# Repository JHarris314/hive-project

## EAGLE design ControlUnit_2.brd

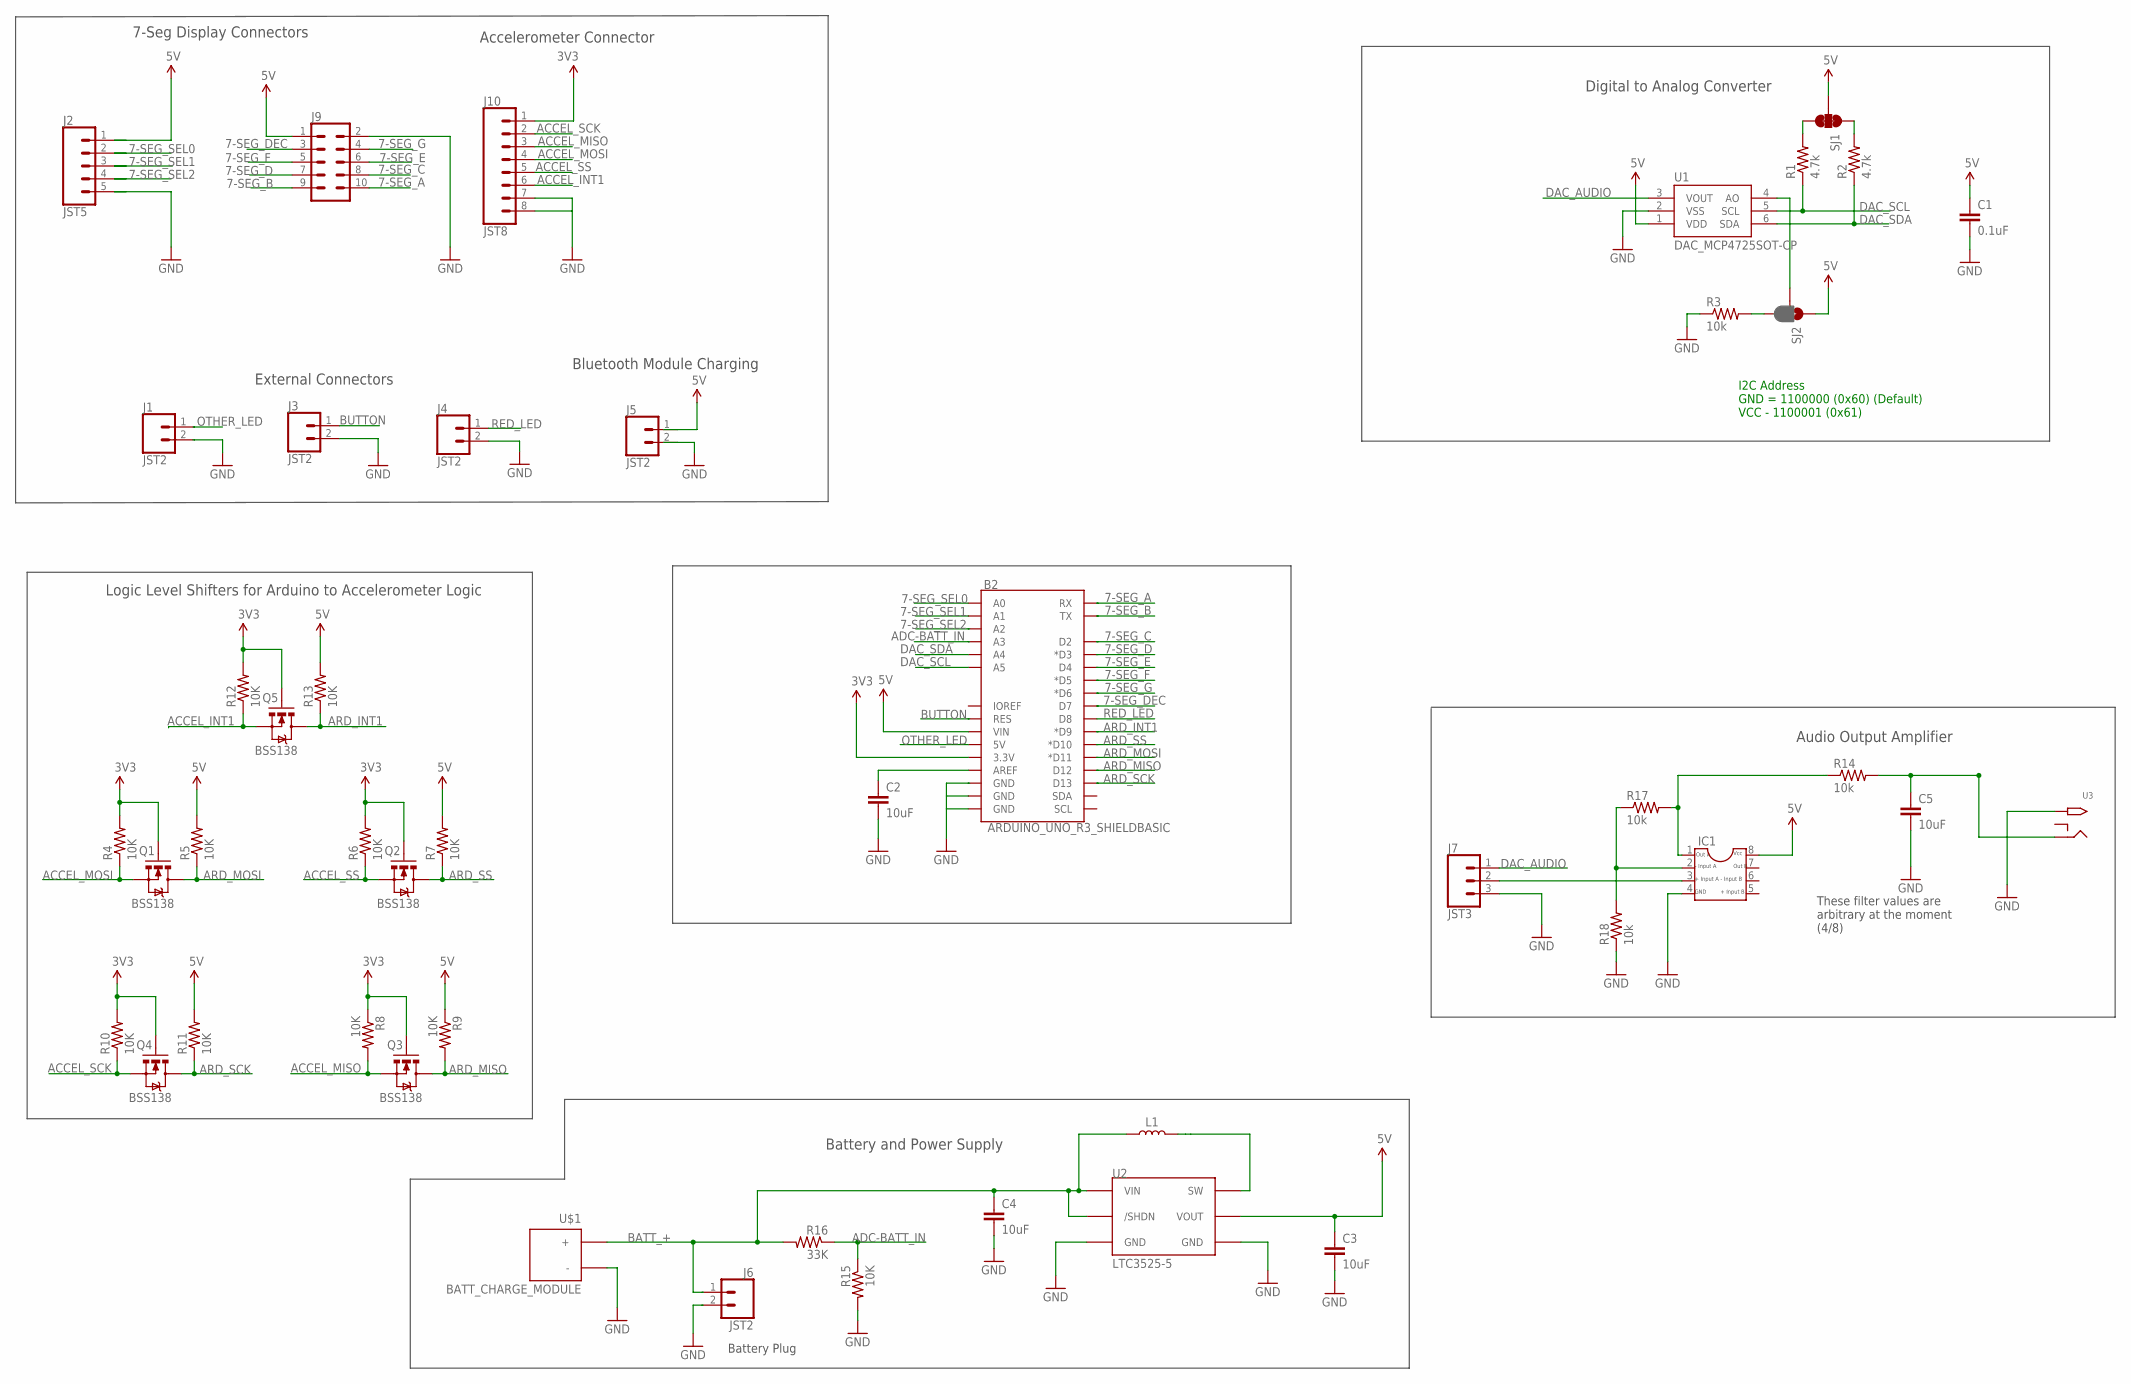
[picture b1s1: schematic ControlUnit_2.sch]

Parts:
B2: ARDUINO_UNO_R3_SHIELDBASIC; UNO_R3_SHIELD
C1: 0.1uF; 0603-CAP
C2, C4: 10uF; SPARKFUN_0805
C3, C5: 10uF; 0603-CAP
IC1: DIL8; DIL08
J1, J3, J4, J5, J6: JST2; 2JST
J2: JST5; 5JST
J7: JST3; 3JST
J9: CONN_05X2SHD_LOCK; 2X5-SHROUDED_LOCK
J10: JST8; 8JST
L1: 10uH; 1210
Q1, Q2, Q3, Q4, Q5: BSS138; SOT23-3
R1, R2: 4.7k; 0603-RES
R3, R14, R17, R18: 10k; 0603-RES
R4, R5, R6, R7, R10, R11, R12, R13: 10K; SPARKFUN_0603-RES
R8, R9, R15: 10K; 0603-RES
R16: 33K; 0603-RES
SJ1: JUMPER-PAD-3-NC_BY_TRACE; PAD-JUMPER-3-3OF3_NC_BY_TRACE_YES_SILK_FULL_BOX
SJ2: JUMPER-PAD-3-2OF3_NC_BY_PASTE; PAD-JUMPER-3-2OF3_NC_BY_PASTE_YES_SILK_FULL_BOX
U1: DAC_MCP4725SOT-CP; SOT23-6-MCP4725
U2: LTC3525-5
U3: MONO_JACK
U$1: BATT_CHARGE_MODULE

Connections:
3V3: B2.3.3V, J10.1, Q1.1 (G), Q2.1 (G), Q3.1 (G), Q4.1 (G), Q5.1 (G), R4.2, R6.2, R8.1, R10.2, R12.2
5V: B2.VIN, C1.1, C3.1, IC1.8, J2.1, J5.1, J9.1, R5.2, R7.2, R9.1, R11.2, R13.2, SJ1.2, SJ2.1, U1.1 (VDD), U2.4 (VOUT)
7-SEG_A: B2.RX, J9.10
7-SEG_B: B2.TX, J9.9
7-SEG_C: B2.D2, J9.8
7-SEG_D: B2.D3 (*D3), J9.7
7-SEG_DEC: B2.D7, J9.3
7-SEG_E: B2.D4, J9.6
7-SEG_F: B2.D5 (*D5), J9.5
7-SEG_G: B2.D6 (*D6), J9.4
7-SEG_SEL0: B2.A0, J2.2
7-SEG_SEL1: B2.A1, J2.3
7-SEG_SEL2: B2.A2, J2.4
ACCEL_INT1: J10.6, Q5.2 (S), R12.1
ACCEL_MISO: J10.3, Q3.2 (S), R8.2
ACCEL_MOSI: J10.4, Q1.2 (S), R4.1
ACCEL_SCK: J10.2, Q4.2 (S), R10.1
ACCEL_SS: J10.5, Q2.2 (S), R6.1
ADC-BATT_IN: B2.A3, R15.1, R16.1
ARD_INT1: B2.D9 (*D9), Q5.3 (D), R13.1
ARD_MISO: B2.D12, Q3.3 (D), R9.2
ARD_MOSI: B2.D11 (*D11), Q1.3 (D), R5.1
ARD_SCK: B2.D13, Q4.3 (D), R11.1
ARD_SS: B2.D10 (*D10), Q2.3 (D), R7.1
BATT_+: C4.1, J6.1, L1.1, R16.2, U2.1 (/SHDN), U2.3 (VIN), U$1.P$2 (+)
BUTTON: B2.RES, J3.1
DAC_AUDIO: J7.1, U1.3 (VOUT)
DAC_SCL: B2.A5, R1.1, U1.5 (SCL)
DAC_SDA: B2.A4, R2.1, U1.6 (SDA)
GND: B2.GND@0 (GND), B2.GND@1 (GND), B2.GND@2 (GND), C1.2, C2.2, C3.2, C4.2, C5.2, IC1.4, J1.2, J2.5, J3.2, J4.2, J5.2, J6.2, J7.3, J9.2, J10.7, J10.8, R3.1, R15.2, R18.1, U1.2 (VSS), U2.2 (GND), U2.5 (GND), U3.1, U$1.P$1 (-)
unnamed: R2.2, SJ1.1
unnamed: R1.2, SJ1.3
unnamed: SJ2.2, U1.4 (AO)
unnamed: R3.2, SJ2.3
unnamed: IC1.1, R14.1, R17.2
unnamed: L1.2, U2.6 (SW)
unnamed: C5.1, R14.2, U3.2
unnamed: IC1.3, J7.2
unnamed: B2.AREF, C2.1
unnamed: IC1.2, R17.1, R18.2
OTHER_LED: B2.5V, J1.1
RED_LED: B2.D8, J4.1

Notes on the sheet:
I2C Address GND = 1100000 (0x60) (Default) VCC - 1100001 (0x61)
Logic Level Shifters for Arduino to Accelerometer Logic
Accelerometer Connector
7-Seg Display Connectors
External Connectors
Battery and Power Supply
Digital to Analog Converter
Audio Output Amplifier
Bluetooth Module Charging
Battery Plug
These filter values are arbitrary at the moment (4/8)

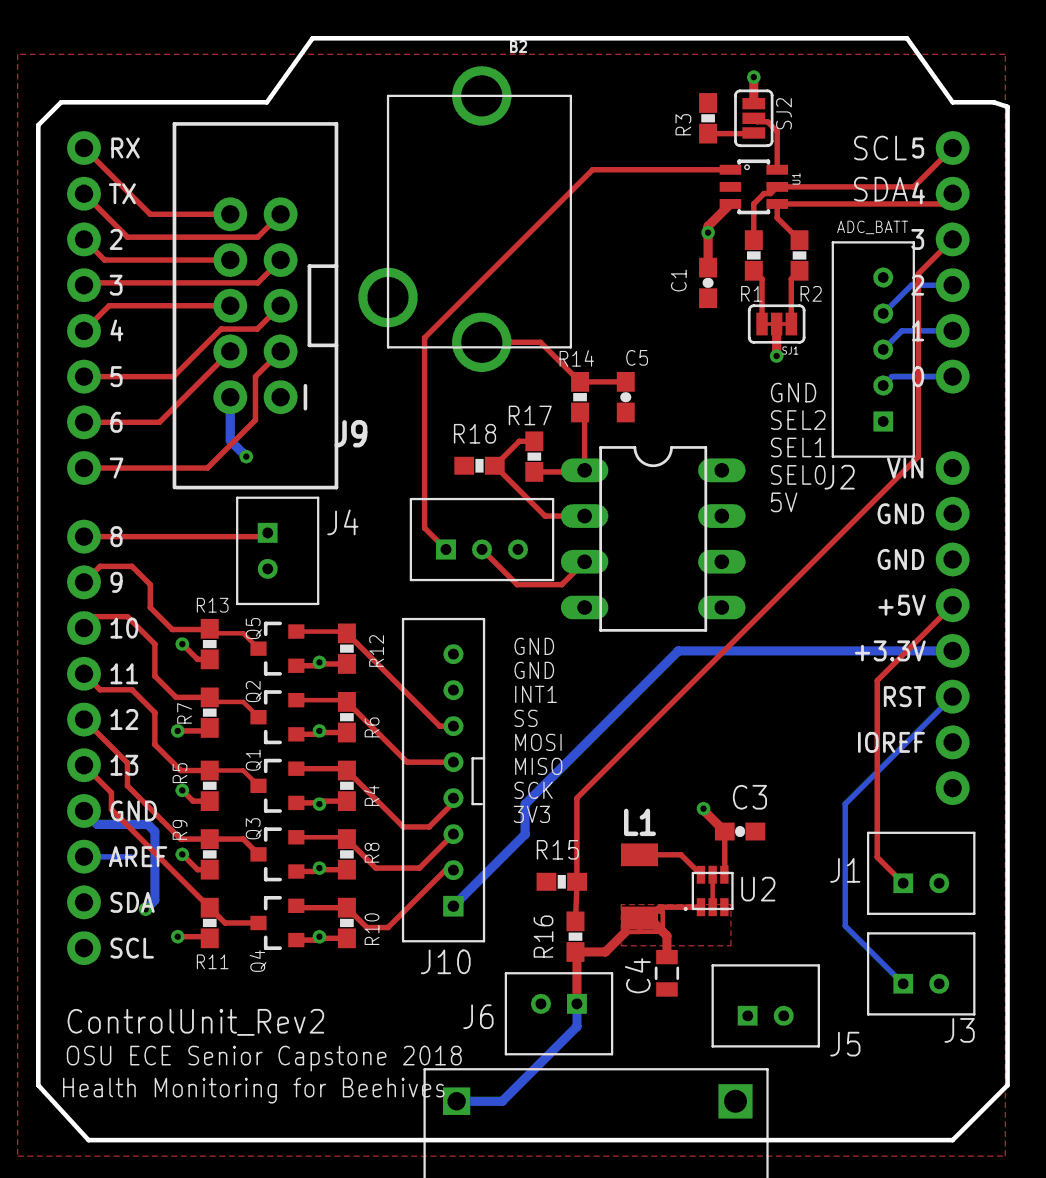
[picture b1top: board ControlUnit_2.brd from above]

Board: 2 copper layers, 53.8 x 61.2 mm, 46 parts (1 on the bottom side), 42 nets.

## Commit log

2018-05-22 final commit
2018-05-23 Create Code

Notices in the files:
parts and their libraries:
SparkFun-AnalogIC: Licensing:Creative Commons ShareAlike 4.0 International - https://creativecommons.org/licenses/by-sa/4.0
